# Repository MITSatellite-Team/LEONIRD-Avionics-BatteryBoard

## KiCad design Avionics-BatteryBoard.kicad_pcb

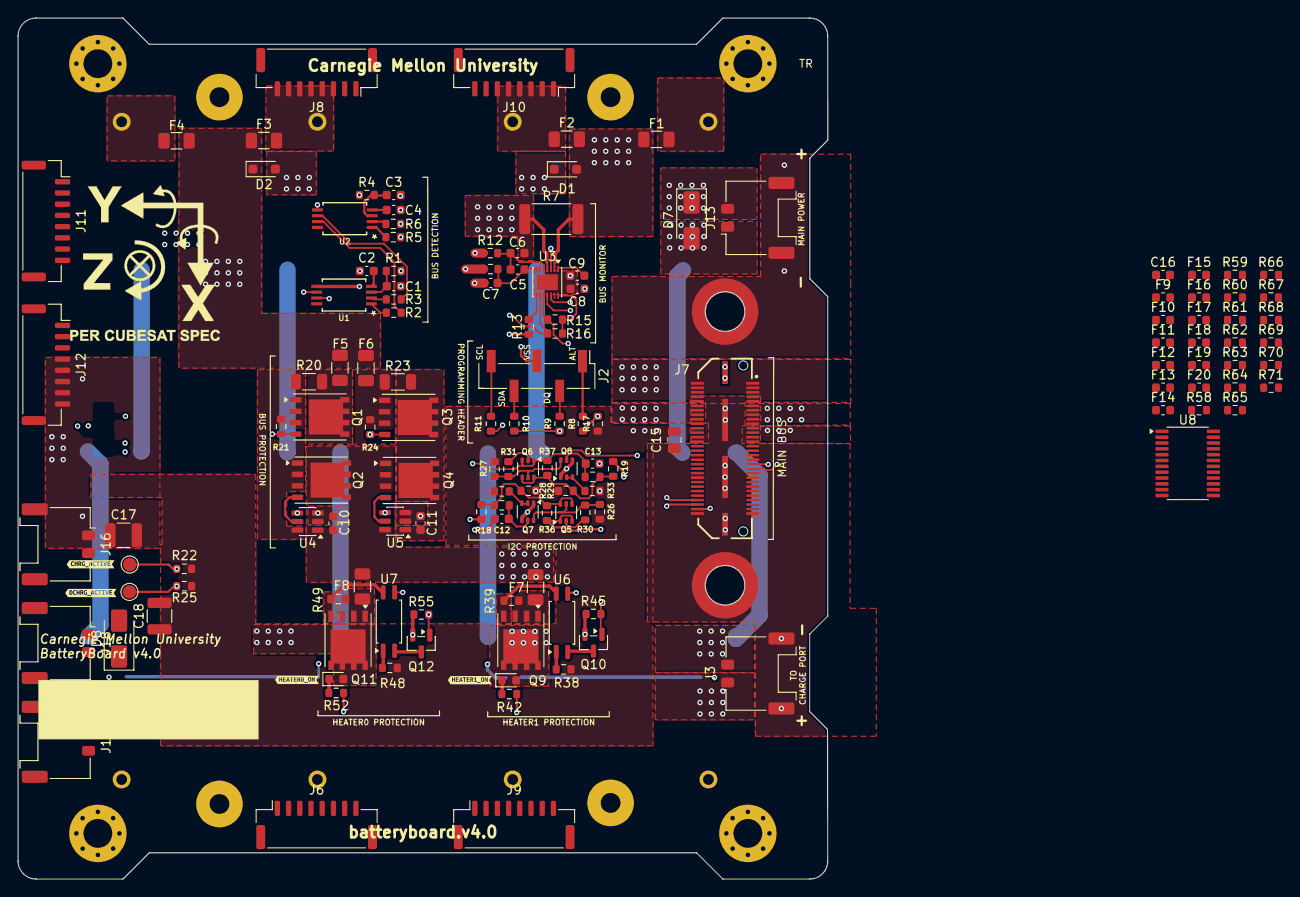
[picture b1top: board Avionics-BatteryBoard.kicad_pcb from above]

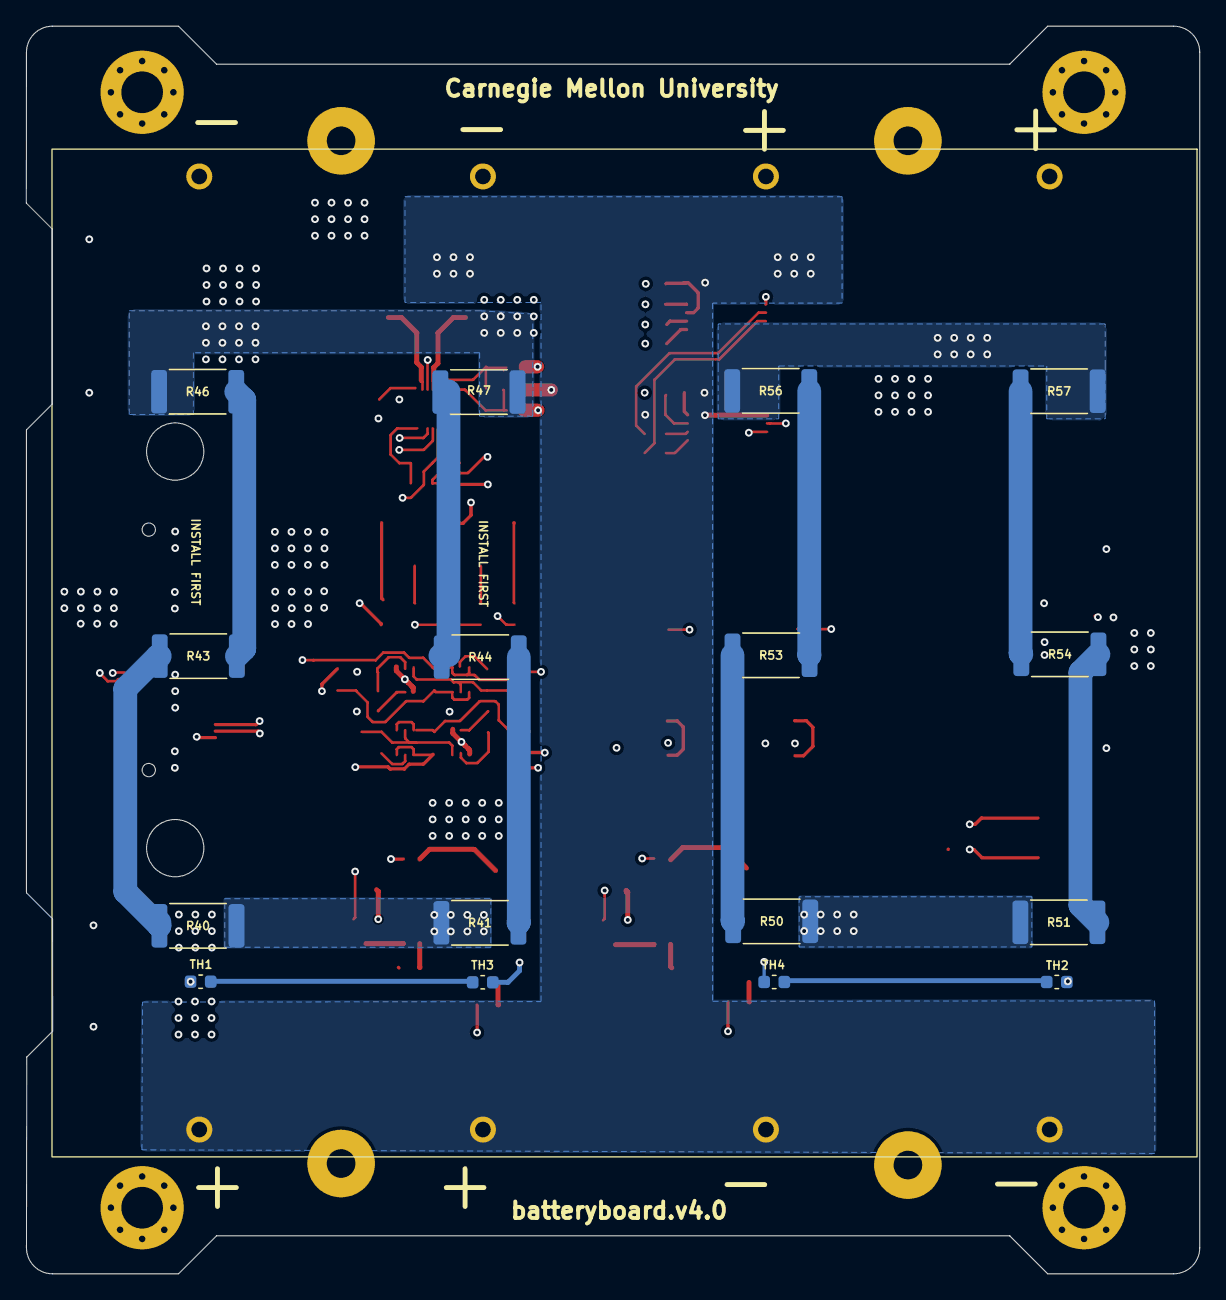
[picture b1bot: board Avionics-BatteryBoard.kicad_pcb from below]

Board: 4 copper layers, 90.2 x 95.9 mm, 164 parts (17 on the bottom side), 110 nets.

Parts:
C1, C3, C6, C10, C11, C16: 100n; C_0603_1608Metric
C2, C4, C12, C13: 10n; C_0603_1608Metric
C5, C7: 1n; C_0603_1608Metric
C8, C9: 470n; C_0603_1608Metric
C15: 10u; C_0805_2012Metric
C17, C18: 22u; C_1210_3225Metric
D1, D2: BAT60JFILM; D_SOD-323_HandSoldering
D5, D6: GREEN; LED_0603_1608Metric
D7, D8: SMAJ9.0AHR3G; D_SMA
F1, F2, F3, F4: 5A; Fuse_1206_3216Metric
F5, F6: 6A; Fuse_1206_3216Metric
F7, F8: 2A; Fuse_1206_3216Metric
F9, F11, F13, F15, F17, F19: 2A; Fuse_0603_1608Metric
F10, F12, F14, F16, F18, F20: 250mA; Fuse_0603_1608Metric
H1, H2, H3, H4: MountingHole_Pad; MountingHole_3.2mm_M3_Pad_Via
J1: 21700 Holder; 21700_battery_holder_th
J2: Fuel Gauge Programming Header; PinHeader_1x05_P2.54mm_Vertical_SMD_Pin1Left
J3, J13, J14, J16, J18: 205338-0002; Molex_Pico-Lock_205338-0002_1x02-1MP_P2.00mm_Horizontal
J6, J8, J9, J10, J11, J12: SM08B-GHS-TB; JST_GH_SM08B-GHS-TB_1x08-1MP_P1.25mm_Horizontal
J7: QTH-030-01-L-D-A; SAMTEC-QTH-030-01-L-D-A
MP1, MP2: M3 x 5mm; WA-SMSI_9774050360
Q1, Q2, Q3, Q4, Q9, Q11: SIRA99DP-T1-GE3; PowerPAK_SO-8_Single
Q5, Q6: MBT2222ADW1T1; SOT-363_SC-70-6
Q7, Q8: NX3008NBKS; SOT-363_SC-70-6
Q10, Q12: IRLML2803; SOT-23
R1, R4: 470R; R_0603_1608Metric
R2, R3, R5, R6, R13, R38, R48: 1k; R_0603_1608Metric
R7: 10m; R_2512_6332Metric
R8: 51k1; R_0603_1608Metric
R9, R10, R11: 150R; R_0603_1608Metric
R12: 10R; R_0603_1608Metric
R14: 100R; R_0603_1608Metric
R15, R16: 30k; R_0603_1608Metric
R17, R26, R27, R28, R29, R42, R45, R52, R55, R58, R59, R60, R61, R62, R63, R64, R65, R66, R67, R68, R69, R70, R71: 10k; R_0603_1608Metric
R18, R19, R36, R37: 0R; R_0603_1608Metric
R20, R23: 0R; R_1206_3216Metric
R21, R24, R32, R33: 100k; R_0603_1608Metric
R22, R25: 470k; R_0603_1608Metric
R30, R31: 680R; R_0603_1608Metric
R34, R35: 200k; R_0603_1608Metric
R39, R49: 4k7; R_0603_1608Metric
R40, R41, R43, R44, R46, R47, R50, R51, R53, R54, R56, R57: 10R; R_2512_6332Metric
TH1, TH2, TH3, TH4: 10k 3435k; C_0603_1608Metric
TP1, TP2: TestPoint; TestPoint_Pad_D1.5mm
U1, U2: S-8209AAA-T8T1U; TSSOP8-E-PKG_FT008-A-P-SD-1.2_ABL
U3: MAX17205; TDFN-14-1EP_3x3mm_P0.4mm_EP1.78x2.35mm
U4, U5: LTC4412xS6; TSOT-23-6
U6, U7: TLX9000; SOIC-4_4.55x2.6mm_P1.27mm
U8: TCA9548APWR; TSSOP-24_4.4x7.8mm_P0.65mm
kibuzzard-6A91DD5B: G***; kibuzzard-6A91DD5B
kibuzzard-6A91DD42: G***; kibuzzard-6A91DD42
kibuzzard-6A825BB0: G***; kibuzzard-6A825BB0
kibuzzard-6A825BF2: G***; kibuzzard-6A825BF2

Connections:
+3V3: C15.1, C16.1, F10.1, F12.1, F14.1, F16.1, F18.1, F20.1, J7.21, J7.22, J7.23, J7.24, R17.2, R22.1, R25.1, R26.1, R27.1, R28.1, R29.1, R32.1, R33.1, R38.2, R48.2, R58.1, R59.1, R60.1, R62.1, R63.1, R64.1, R65.1, R66.1, R67.1, R68.1, R69.1, R70.1, R71.1, U8.24 (VCC)
/Battery Bus Detection/BATT_M: C1.2, C2.2, D1.1 (K), D2.2 (A), J1.5 (NEG), J1.6 (NEG), J1.7 (POS), J1.8 (POS), R4.1, R14.1, U1.5 (VSS)
/Battery Bus Detection/BATT_N: C3.2, C4.2, C7.2, D1.2 (A), F1.2, F2.2, R5.2, R6.2, R7.2, U2.5 (VSS), U3.2 (CSP)
/Battery Bus Detection/BATT_P: D2.1 (K), F3.1, F4.1, F5.1, F6.2, R1.1, R12.1
/Battery Bus Detection/CHARGE_EN: Q1.4 (G), R21.2, U1.7 (CO)
/Battery Bus Detection/DISCHARGE_EN: Q3.4 (G), R24.2, U1.6 (DO)
/Battery Bus Protection/CHARGE_ACTIVE: R22.2, TP1.1 (1_1), U4.4 (STAT)
/Battery Bus Protection/DISCHARGE_ACTIVE: R25.2, TP2.1 (1_1), U5.4 (STAT)
/Battery Monitor/A: J2.1, R8.2
/Battery Monitor/ALERT: J7.58, R8.1, R13.2, R17.1
/Battery Monitor/C: J2.5, R11.2
/Battery Monitor/D: J2.4, R10.2
/Battery Monitor/DQ: J2.2, R9.2
/Battery Monitor/I2C Protection/SCL_DEVICE: Q5.4 (E2), Q5.6 (C1), R18.2, R28.2, R34.1, R36.1
/Battery Monitor/I2C Protection/SDA_DEVICE: Q6.4 (E2), Q6.6 (C1), R19.1, R29.2, R35.1, R37.1
/Battery Monitor/SCL: R11.1, R18.1, U3.11 (SCL)
/Battery Monitor/SCL_FUEL: J7.37, Q5.1 (E1), Q5.3 (C2), R36.2, U8.22 (SCL)
/Battery Monitor/SDA: R9.1, R10.1, R19.2, U3.12 (SDA)
/Battery Monitor/SDA_FUEL: J7.39, Q6.1 (E1), Q6.3 (C2), R37.2, U8.23 (SDA)
/Battery Temperature Protection/BatteryHeater1/V_HEATER: D5.2 (A), Q9.5 (D), R40.2, R41.2
/Battery Temperature Protection/BatteryHeater/V_HEATER: D6.2 (A), Q11.5 (D), R50.2, R51.2
/Battery Temperature Protection/HEATER0_ON: J7.54, Q12.1 (G), R55.2
/Battery Temperature Protection/HEATER1_ON: J7.56, Q10.1 (G), R45.2
/Interfaces/MUX_RST: J7.42, R60.2, U8.3 (~RESET)
/Solar Panels/3V3_NX: F12.2, J8.4
/Solar Panels/3V3_NY: F16.2, J10.4
/Solar Panels/3V3_NZ: F20.2, J12.4
/Solar Panels/3V3_PX: F10.2, J6.4
/Solar Panels/3V3_PY: F14.2, J9.4
/Solar Panels/3V3_PZ: F18.2, J11.4
/Solar Panels/COIL_EN: J6.8, J7.36, J8.8, J9.8, J10.8, J11.8, J12.8, R61.1
/Solar Panels/SCL_NX: J8.6, R62.2, U8.7 (SC1)
/Solar Panels/SCL_NY: J10.6, R66.2, U8.11 (SC3)
/Solar Panels/SCL_NZ: J12.6, R70.2, U8.16 (SC5)
/Solar Panels/SCL_PX: J6.6, R58.2, U8.5 (SC0)
/Solar Panels/SCL_PY: J9.6, R64.2, U8.9 (SC2)
/Solar Panels/SCL_PZ: J11.6, R68.2, U8.14 (SC4)
/Solar Panels/SDA_NX: J8.5, R63.2, U8.6 (SD1)
/Solar Panels/SDA_NY: J10.5, R67.2, U8.10 (SD3)
/Solar Panels/SDA_NZ: J12.5, R71.2, U8.15 (SD5)
/Solar Panels/SDA_PX: J6.5, R59.2, U8.4 (SD0)
/Solar Panels/SDA_PY: J9.5, R65.2, U8.8 (SD2)
/Solar Panels/SDA_PZ: J11.5, R69.2, U8.13 (SD4)
/Solar Panels/VCHRG_NX: F11.1, J8.1, J8.2
/Solar Panels/VCHRG_NY: F15.1, J10.1, J10.2
/Solar Panels/VCHRG_NZ: F19.1, J12.1, J12.2
/Solar Panels/VCHRG_PX: F9.1, J6.1, J6.2
/Solar Panels/VCHRG_PY: F13.1, J9.1, J9.2
/Solar Panels/VCHRG_PZ: F17.1, J11.1, J11.2
GND: C12.2, C13.2, C15.2, C16.2, D7.2 (A), D8.2 (A), H1.1 (1_1), H2.1 (1_1), H3.1 (1_1), H4.1 (1_1), J1.9 (GND), J1.10 (GND), J1.11 (GND), J1.12 (GND), J3.MP (MountPin), J6.3, J6.7, J6.MP (MountPin), J7.11, J7.12, J7.13, J7.14, J7.15, J7.16, J7.17, J7.18, J7.19, J7.20, J7.25, J7.26, J7.27, J7.28, J7.35, J7.41, J7.44, J7.47, J7.59, J7.60, J7.G1 (GND), J7.G2 (GND), J7.G3 (GND), J7.G4 (GND), J8.3, J8.7, J8.MP (MountPin), J9.3, J9.7, J9.MP (MountPin), J10.3, J10.7, J10.MP (MountPin), J11.3, J11.7, J11.MP (MountPin), J12.3, J12.7, J12.MP (MountPin), J13.1, J13.MP (MountPin), J14.2, J14.MP (MountPin), J16.MP (MountPin), J18.MP (MountPin), MP1.1, MP2.1, Q7.1 (S), Q7.4 (S), Q8.1 (S), Q8.4 (S), Q10.2 (S), Q12.2 (S), R45.1, R55.1, R61.2, U8.1 (A0), U8.2 (A1), U8.12 (GND), U8.21 (A2)
unnamed: D5.1 (K), R42.2
unnamed: D6.1 (K), R52.2
unnamed: F1.1, J1.4 (NEG)
unnamed: F2.1, J1.3 (NEG)
unnamed: F3.2, J1.2 (POS)
unnamed: F4.2, J1.1 (POS)
unnamed: F6.1, Q3.1 (S), Q3.2 (S), Q3.3 (S), R23.2, R24.1
unnamed: F7.2, Q9.1 (S), Q9.2 (S), Q9.3 (S), R39.2
unnamed: F8.2, Q11.1 (S), Q11.2 (S), Q11.3 (S), R49.2
unnamed: F5.2, Q1.5 (D), R20.2
unnamed: Q2.4 (G), U4.5 (GATE)
unnamed: C11.1, Q3.5 (D), Q4.5 (D), R23.1, U5.1 (VIN)
unnamed: Q4.4 (G), U5.5 (GATE)
unnamed: Q5.2 (B1), R30.1
unnamed: Q5.5 (B2), Q7.6 (D), R26.2, R30.2
unnamed: Q6.2 (B1), R31.1
unnamed: Q6.5 (B2), Q8.6 (D), R27.2, R31.2
unnamed: Q7.2 (G), Q7.3 (D), R32.2
unnamed: C12.1, Q7.5 (G), R34.2
unnamed: Q8.2 (G), Q8.3 (D), R33.2
unnamed: C13.1, Q8.5 (G), R35.2
unnamed: Q9.4 (G), R39.1, U6.4
unnamed: Q10.3 (D), U6.2
unnamed: Q11.4 (G), R49.1, U7.4
unnamed: Q12.3 (D), U7.2
unnamed: R38.1, U6.1
unnamed: R40.1, R43.2
unnamed: R41.1, R44.2
unnamed: R43.1, R46.2
unnamed: R44.1, R47.2
unnamed: R48.1, U7.1
unnamed: R50.1, R53.2
unnamed: R51.1, R54.2
unnamed: R53.1, R56.2
unnamed: R54.1, R57.2
unnamed: TH1.2, TH3.1
unnamed: TH2.2, TH4.1
unnamed: C2.1, U1.4 (CDT)
unnamed: R2.1, U1.1 (CTLC)
unnamed: R3.1, U1.2 (CTLD)
unnamed: C1.1, R1.2, U1.3 (VDD)
unnamed: C4.1, U2.4 (CDT)
unnamed: R2.2, U2.7 (CO)
unnamed: R5.1, U2.1 (CTLC)
unnamed: R6.1, U2.2 (CTLD)
unnamed: R3.2, U2.6 (DO)
unnamed: C3.1, R4.2, U2.3 (VDD)
unnamed: R16.2, TH2.1, U3.9 (AIN1)
unnamed: R15.2, TH1.1, U3.10 (AIN2)
unnamed: R13.1, U3.8 (ALRT1)
unnamed: C5.2, C7.1, R14.2, U3.6 (CELL2), U3.7 (CELL1)
unnamed: C8.1, U3.3 (REG2)
unnamed: C9.1, U3.1 (REG3)
unnamed: R15.1, R16.1, U3.14 (THRM)
unnamed: C5.1, C6.1, R12.2, U3.5 (VBATT)
unnamed: Q1.1 (S), Q1.2 (S), Q1.3 (S), Q2.1 (S), Q2.2 (S), Q2.3 (S), R20.1, R21.1, U4.6 (SENSE)
SYSTEM_VDD: C10.1, C17.1, C18.1, F7.1, F8.1, J3.2, J16.2, Q2.5 (D), Q4.1 (S), Q4.2 (S), Q4.3 (S), U4.1 (VIN), U5.6 (SENSE)
SYSTEM_VSS: C6.2, C8.2, C9.2, C10.2, C11.2, C17.2, C18.2, J2.3, J3.1, J14.1, R7.1, R42.1, R46.1, R47.1, R52.1, R56.1, R57.1, TH3.2, TH4.2, U3.4 (CSN), U3.15 (GND), U4.2 (GND), U4.3 (CTL), U5.2 (GND), U5.3 (CTL), U6.3, U7.3
VBATT: D7.1 (K), J7.1, J7.2, J7.3, J7.4, J7.5, J7.6, J7.7, J7.8, J7.9, J7.10, J13.2, J18.1
VCHRG: D8.1 (K), F9.2, F11.2, F13.2, F15.2, F17.2, F19.2, J16.1, J18.2
